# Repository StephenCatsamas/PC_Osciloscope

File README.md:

# PC_Osciloscope
An external analog front end to turn a pc sound card into an osciloscope

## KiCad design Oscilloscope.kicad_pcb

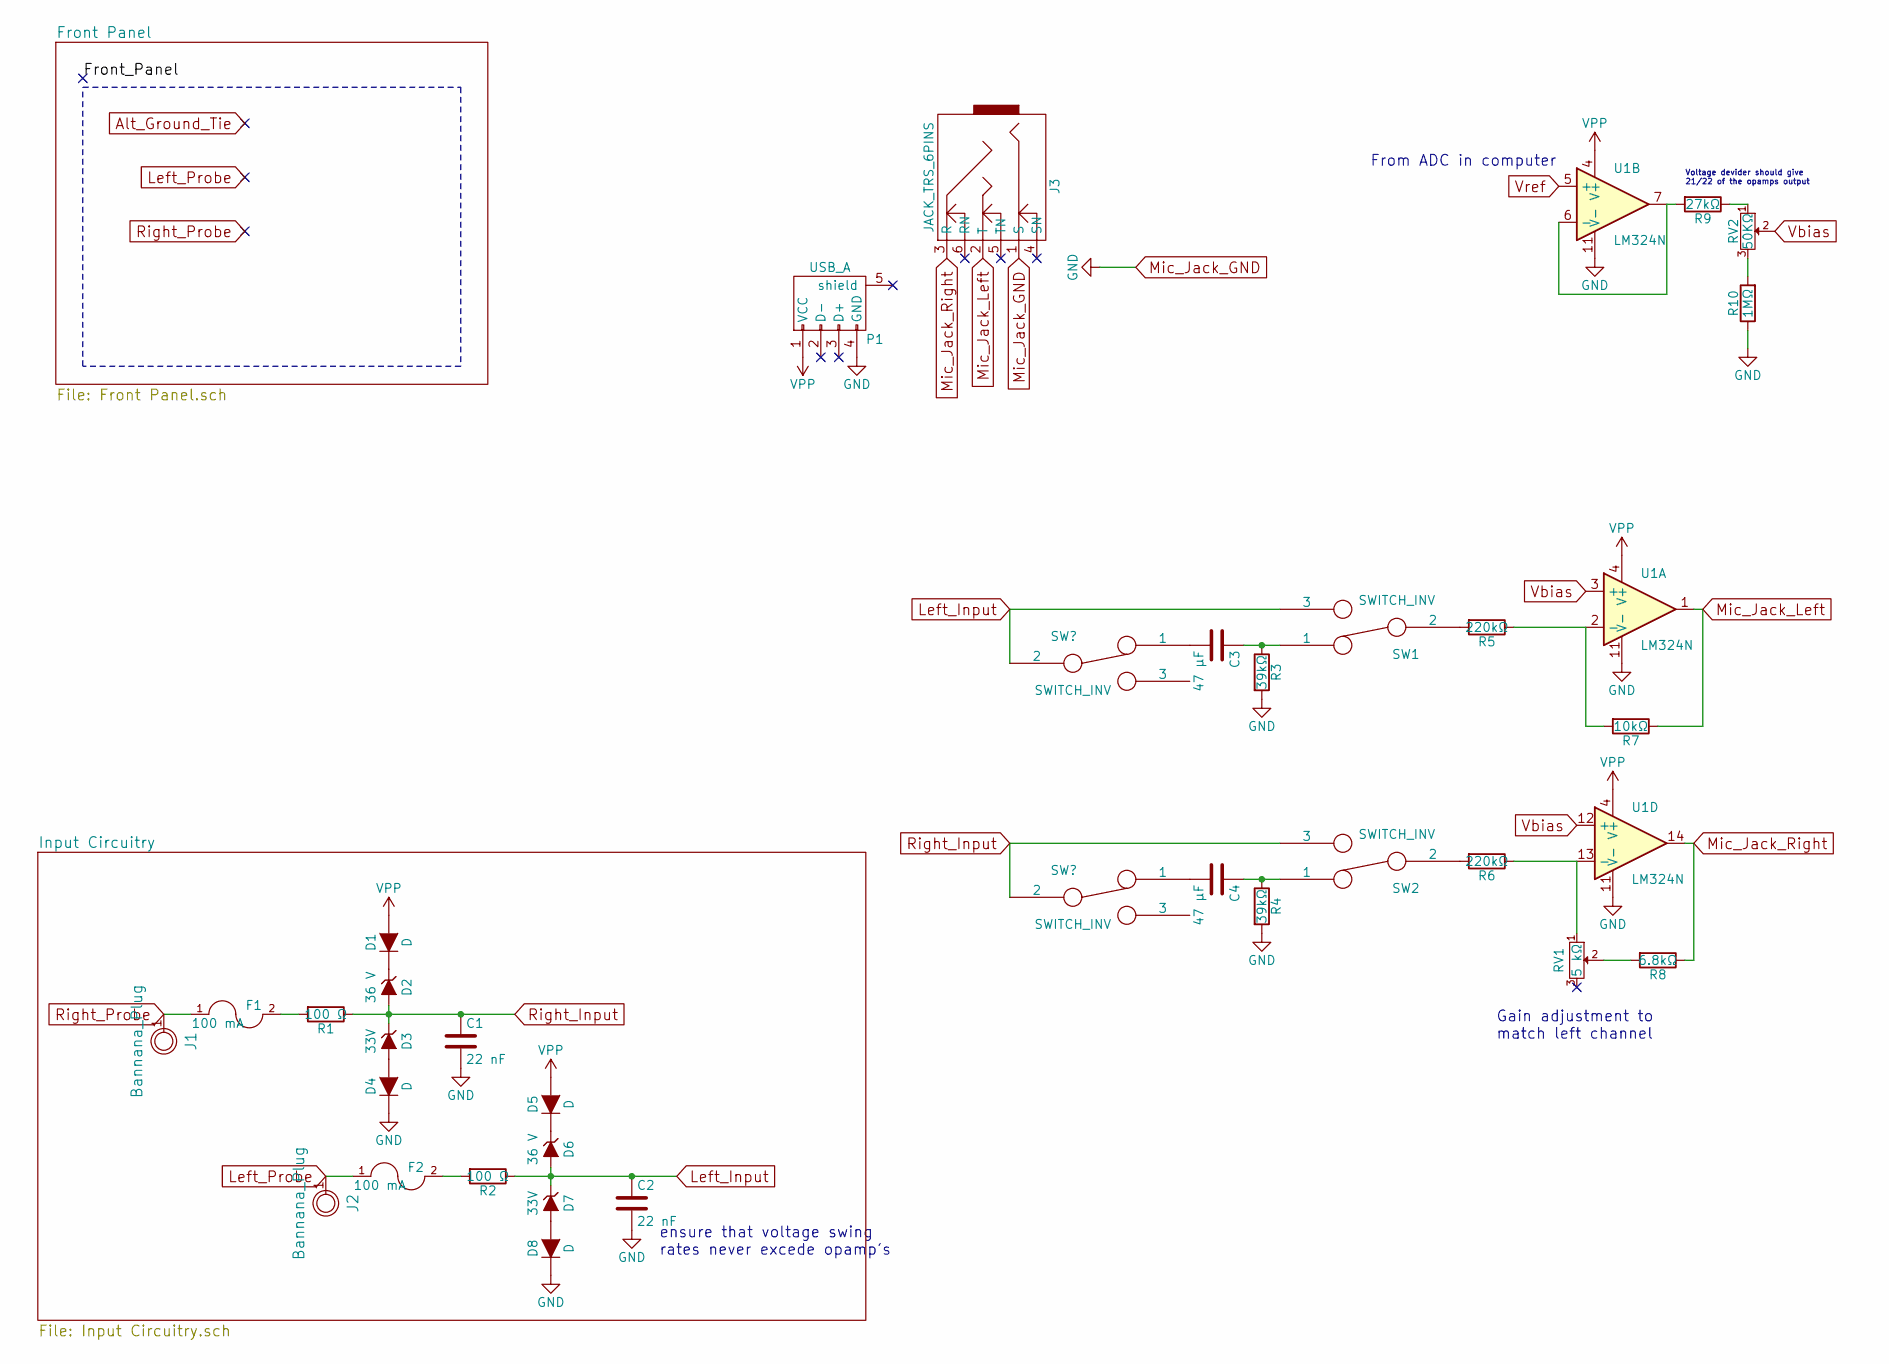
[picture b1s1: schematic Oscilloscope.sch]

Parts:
C1, C2: 22 nF; C_Disc_D7.5mm_W5.0mm_P10.00mm
C3, C4: 47 μF; CP_Radial_D8.0mm_P2.50mm
D1, D4, D5, D8: D; D_A-405_P7.62mm_Horizontal
D2, D6: 36 V; D_A-405_P7.62mm_Horizontal
D3, D7: 33V; D_A-405_P7.62mm_Horizontal
F1, F2: 100 mA; Fuseholder5x20_horiz_open_lateral_Type-II
J1, J2: Bannana_Plug; Banana_Jack_1Pin
J3: JACK_TRS_6PINS; PJ320E_3.5mm_Jack
P1: USB_A
R1, R2: 100 Ω; R_Axial_Power_L20.0mm_W6.4mm_P22.40mm
R3, R4: 39kΩ; R_Axial_DIN0207_L6.3mm_D2.5mm_P10.16mm_Horizontal
R5, R6: 220kΩ; R_Axial_DIN0207_L6.3mm_D2.5mm_P10.16mm_Horizontal
R7: 10kΩ; R_Axial_DIN0207_L6.3mm_D2.5mm_P2.54mm_Vertical
R8: 6.8kΩ; R_Axial_DIN0207_L6.3mm_D2.5mm_P10.16mm_Horizontal
R9: 27kΩ; R_Axial_DIN0207_L6.3mm_D2.5mm_P15.24mm_Horizontal
R10: 1MΩ; R_Axial_DIN0207_L6.3mm_D2.5mm_P10.16mm_Horizontal
RV1: 5 kΩ; Potentiometer_Trimmer_Bourns_3006W
RV2: 50KΩ; Potentiometer_Trimmer_Bourns_3006W
SW1, SW2: SWITCH_INV; SW_E-Switch_EG1224_SPDT_Angled
U1: LM324N; DIP-14_W10.16mm

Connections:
Left_Input: C2.1, C3.2, D6.2 (A), D7.1 (K), R2.1, SW1.3
Left_Probe: F2.1, J2.1
Mic_Jack_GND: C1.2, C2.2, D4.1 (K), D8.1 (K), J3.1 (S), P1.4 (GND), R3.2, R4.2, R10.1, U1.11 (V-)
Mic_Jack_Left: J3.2 (T), R7.1, U1.1
Mic_Jack_Right: J3.3 (R), R8.1, U1.14
unnamed: C3.1, R3.1, SW1.1
unnamed: C4.1, R4.1, SW2.1
unnamed: D1.1 (K), D2.1 (K)
unnamed: D3.2 (A), D4.2 (A)
unnamed: D5.1 (K), D6.1 (K)
unnamed: D7.2 (A), D8.2 (A)
unnamed: F1.2, R1.2
unnamed: F2.2, R2.2
unnamed: R5.1, R7.2, U1.2 (-)
unnamed: R5.2, SW1.2
unnamed: R6.1, RV1.1, U1.13 (-)
unnamed: R6.2, SW2.2
unnamed: R8.2, RV1.2
unnamed: R9.1, RV2.1
unnamed: R9.2, U1.6 (-), U1.7
unnamed: R10.2, RV2.3
Right_Input: C1.1, C4.2, D2.2 (A), D3.1 (K), R1.1, SW2.3
Right_Probe: F1.1, J1.1
VPP: D1.2 (A), D5.2 (A), P1.1 (VCC), U1.4 (V+)
Vbias: RV2.2, U1.3 (+), U1.12 (+)

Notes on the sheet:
Voltage devider should give 21/22 of the opamps output
ensure that voltage swing rates never excede opamp's
Gain adjustment to match left channel
From ADC in computer

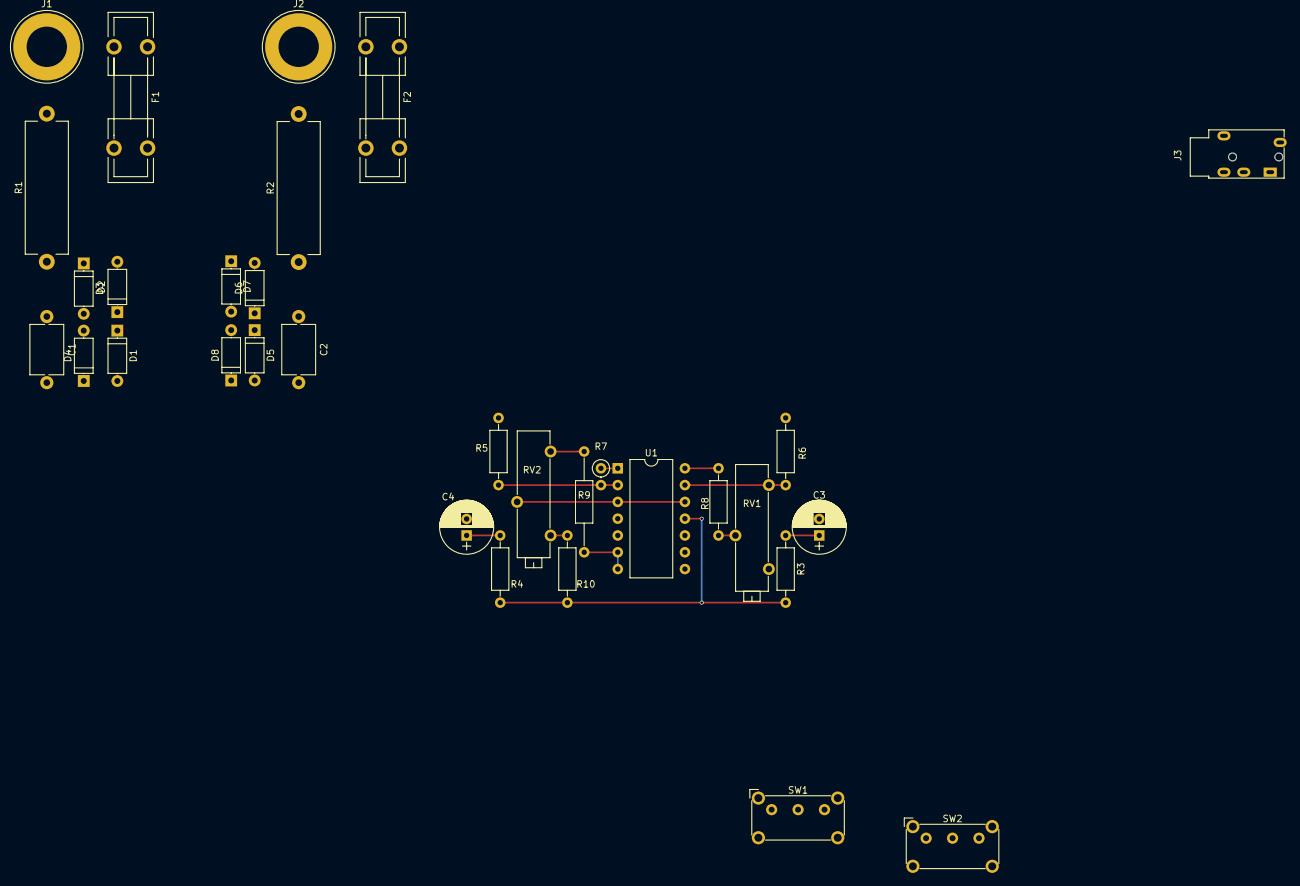
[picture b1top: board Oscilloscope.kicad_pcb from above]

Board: 4 copper layers, 32 parts (0 on the bottom side), 25 nets.

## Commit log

2019-12-29 Archive retroactive upload of project
2019-12-30 added display image
